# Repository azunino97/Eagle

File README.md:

# Eagle
Public repo for displaying my personal embedded design projects using Eagle, a PCB CAD software!

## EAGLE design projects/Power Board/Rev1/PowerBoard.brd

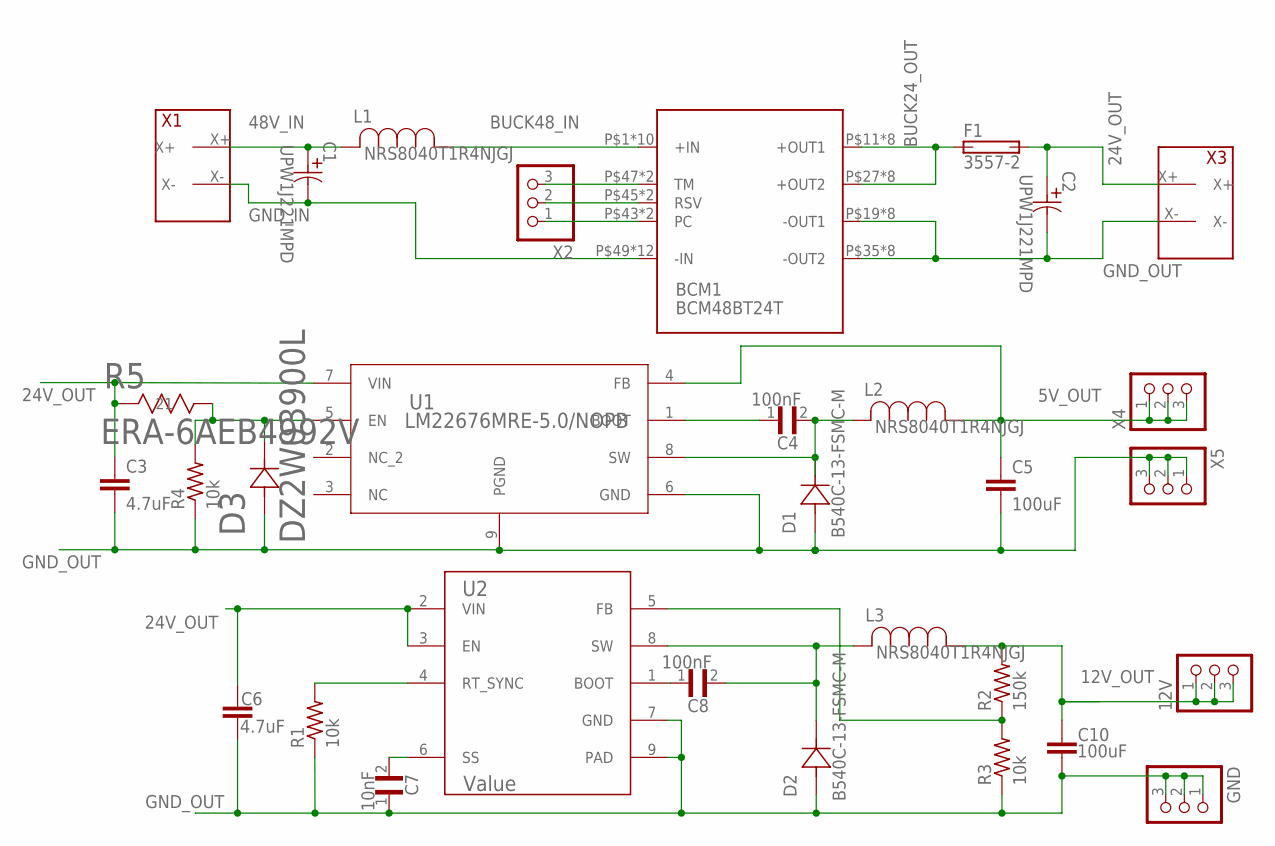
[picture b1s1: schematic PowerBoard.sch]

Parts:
12V: 9-146281-0; TE_9-146281-0
BCM1: BCM48BT24T
C1, C2: UPW1J221MPD; PCAP_10X20-THRU-ELECT
C3, C6: 4.7uF; 0603
C4, C8: 100nF; CAPC2012X135N
C5, C10: 100uF; 1210
C7: 10nF; CAPC2012X135N
D1, D2: B540C-13-FSMC-M; SMC-M
D3: DZ2W03900L; MINI2-F3-B
F1: 3557-2; FUSE_3557-2
GND: 9-146281-0; TE_9-146281-0
L1, L2, L3: NRS8040T1R4NJGJ; IND_TAIYO_NRS8040
R1, R3, R4: 10k; R0603
R2: 150k; R0603
R5: ERA-6AEB4992V; RES_ERA6A_0805
U1: LM22676MRE-5.0/NOPB; MRA08B
U2: Value; DDA0008E_N
X1, X3: XT60
X2, X4, X5: 9-146281-0; TE_9-146281-0

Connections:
5V_OUT: C5.1, L2.1, U1.4 (FB), X4.1, X4.2, X4.3
12V_OUT: 12V.1, 12V.2, 12V.3, C10.1, L3.1, R2.2
24V_OUT: C2.1 (11), C3.1, C6.1, F1.3 (2A), F1.4 (2A), R5.2 (21), U1.7 (VIN), U2.2 (VIN), U2.3 (EN), X3.X+
48V_IN: C1.1 (11), L1.2, X1.X+
BUCK24_OUT: BCM1.P$11 (+OUT1), BCM1.P$12 (+OUT1), BCM1.P$13 (+OUT1), BCM1.P$14 (+OUT1), BCM1.P$15 (+OUT1), BCM1.P$16 (+OUT1), BCM1.P$17 (+OUT1), BCM1.P$18 (+OUT1), BCM1.P$27 (+OUT2), BCM1.P$28 (+OUT2), BCM1.P$29 (+OUT2), BCM1.P$30 (+OUT2), BCM1.P$31 (+OUT2), BCM1.P$32 (+OUT2), BCM1.P$33 (+OUT2), BCM1.P$34 (+OUT2), F1.1 (1A), F1.2 (1A)
BUCK48_IN: BCM1.P$1 (+IN), BCM1.P$2 (+IN), BCM1.P$3 (+IN), BCM1.P$4 (+IN), BCM1.P$5 (+IN), BCM1.P$6 (+IN), BCM1.P$7 (+IN), BCM1.P$8 (+IN), BCM1.P$9 (+IN), BCM1.P$10 (+IN), L1.1
GND_IN: BCM1.P$49 (-IN), BCM1.P$50 (-IN), BCM1.P$51 (-IN), BCM1.P$52 (-IN), BCM1.P$53 (-IN), BCM1.P$54 (-IN), BCM1.P$55 (-IN), BCM1.P$56 (-IN), BCM1.P$57 (-IN), BCM1.P$58 (-IN), BCM1.P$59 (-IN), BCM1.P$60 (-IN), C1.2 (22), X1.X-
GND_OUT: BCM1.P$19 (-OUT1), BCM1.P$20 (-OUT1), BCM1.P$21 (-OUT1), BCM1.P$22 (-OUT1), BCM1.P$23 (-OUT1), BCM1.P$24 (-OUT1), BCM1.P$25 (-OUT1), BCM1.P$26 (-OUT1), BCM1.P$35 (-OUT2), BCM1.P$36 (-OUT2), BCM1.P$37 (-OUT2), BCM1.P$38 (-OUT2), BCM1.P$39 (-OUT2), BCM1.P$40 (-OUT2), BCM1.P$41 (-OUT2), BCM1.P$42 (-OUT2), C2.2 (22), C3.2, C5.2, C6.2, C7.1, C10.2, D1.2 (21), D2.2 (21), D3.2 (22), GND.1, GND.2, GND.3, R1.1, R3.1, R4.1, U1.6 (GND), U1.9 (PGND), U2.7 (GND), U2.9 (PAD), X3.X-, X5.1, X5.2, X5.3
unnamed: C4.1, U1.1 (BOOT)
unnamed: D3.1 (11), R4.2, R5.1 (12), U1.5 (EN)
unnamed: BCM1.P$43 (PC), BCM1.P$44 (PC), X2.1
unnamed: C4.2, D1.1 (12), L2.2, U1.8 (SW)
unnamed: BCM1.P$45 (RSV), BCM1.P$46 (RSV), X2.2
unnamed: BCM1.P$47 (TM), BCM1.P$48 (TM), X2.3
unnamed: C7.2, U2.6 (SS)
unnamed: R1.2, U2.4 (RT_SYNC)
unnamed: C8.1, U2.1 (BOOT)
unnamed: C8.2, D2.1 (12), L3.2, U2.8 (SW)
unnamed: R2.1, R3.2, U2.5 (FB)

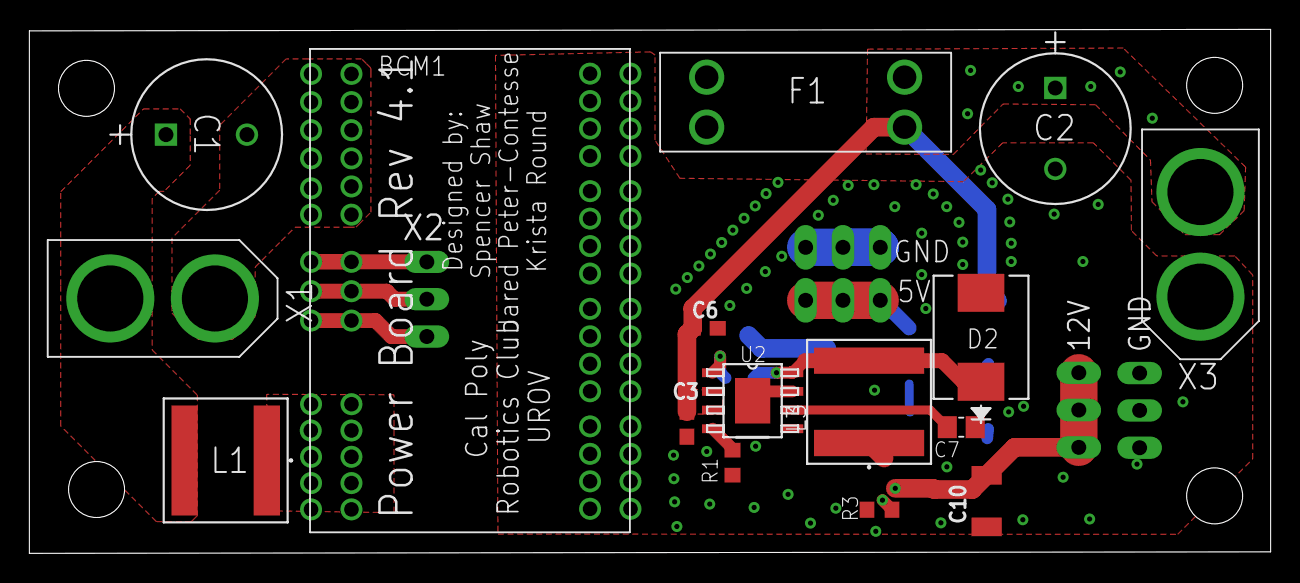
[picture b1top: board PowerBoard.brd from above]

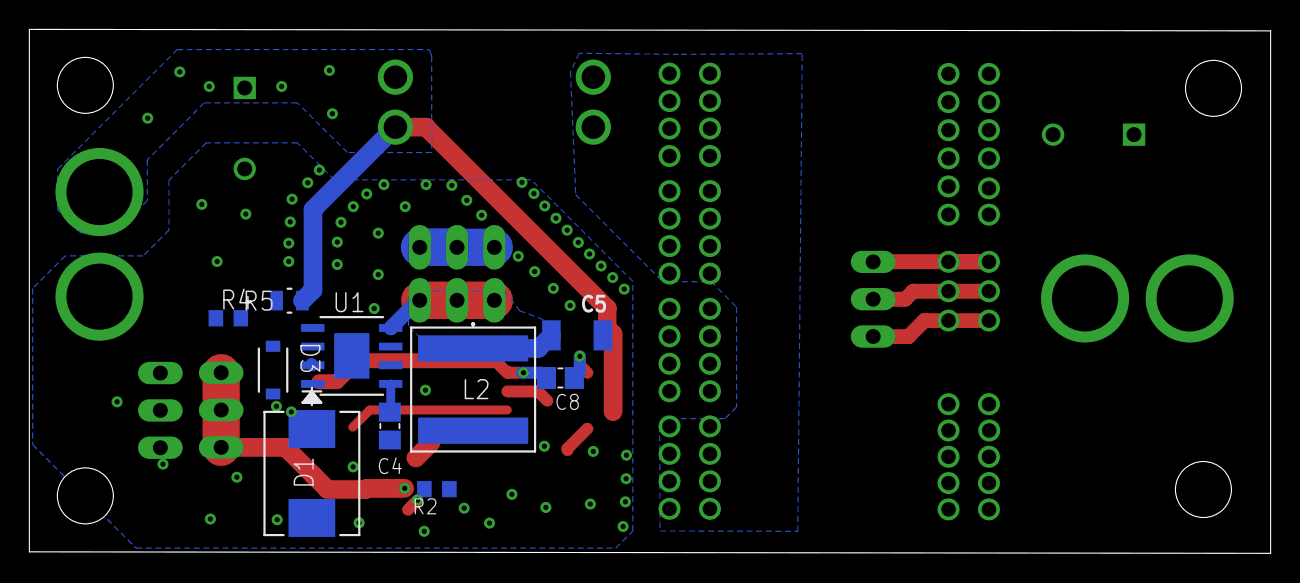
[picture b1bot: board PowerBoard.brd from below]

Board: 2 copper layers, 84.5 x 35.7 mm, 31 parts (12 on the bottom side), 19 nets.

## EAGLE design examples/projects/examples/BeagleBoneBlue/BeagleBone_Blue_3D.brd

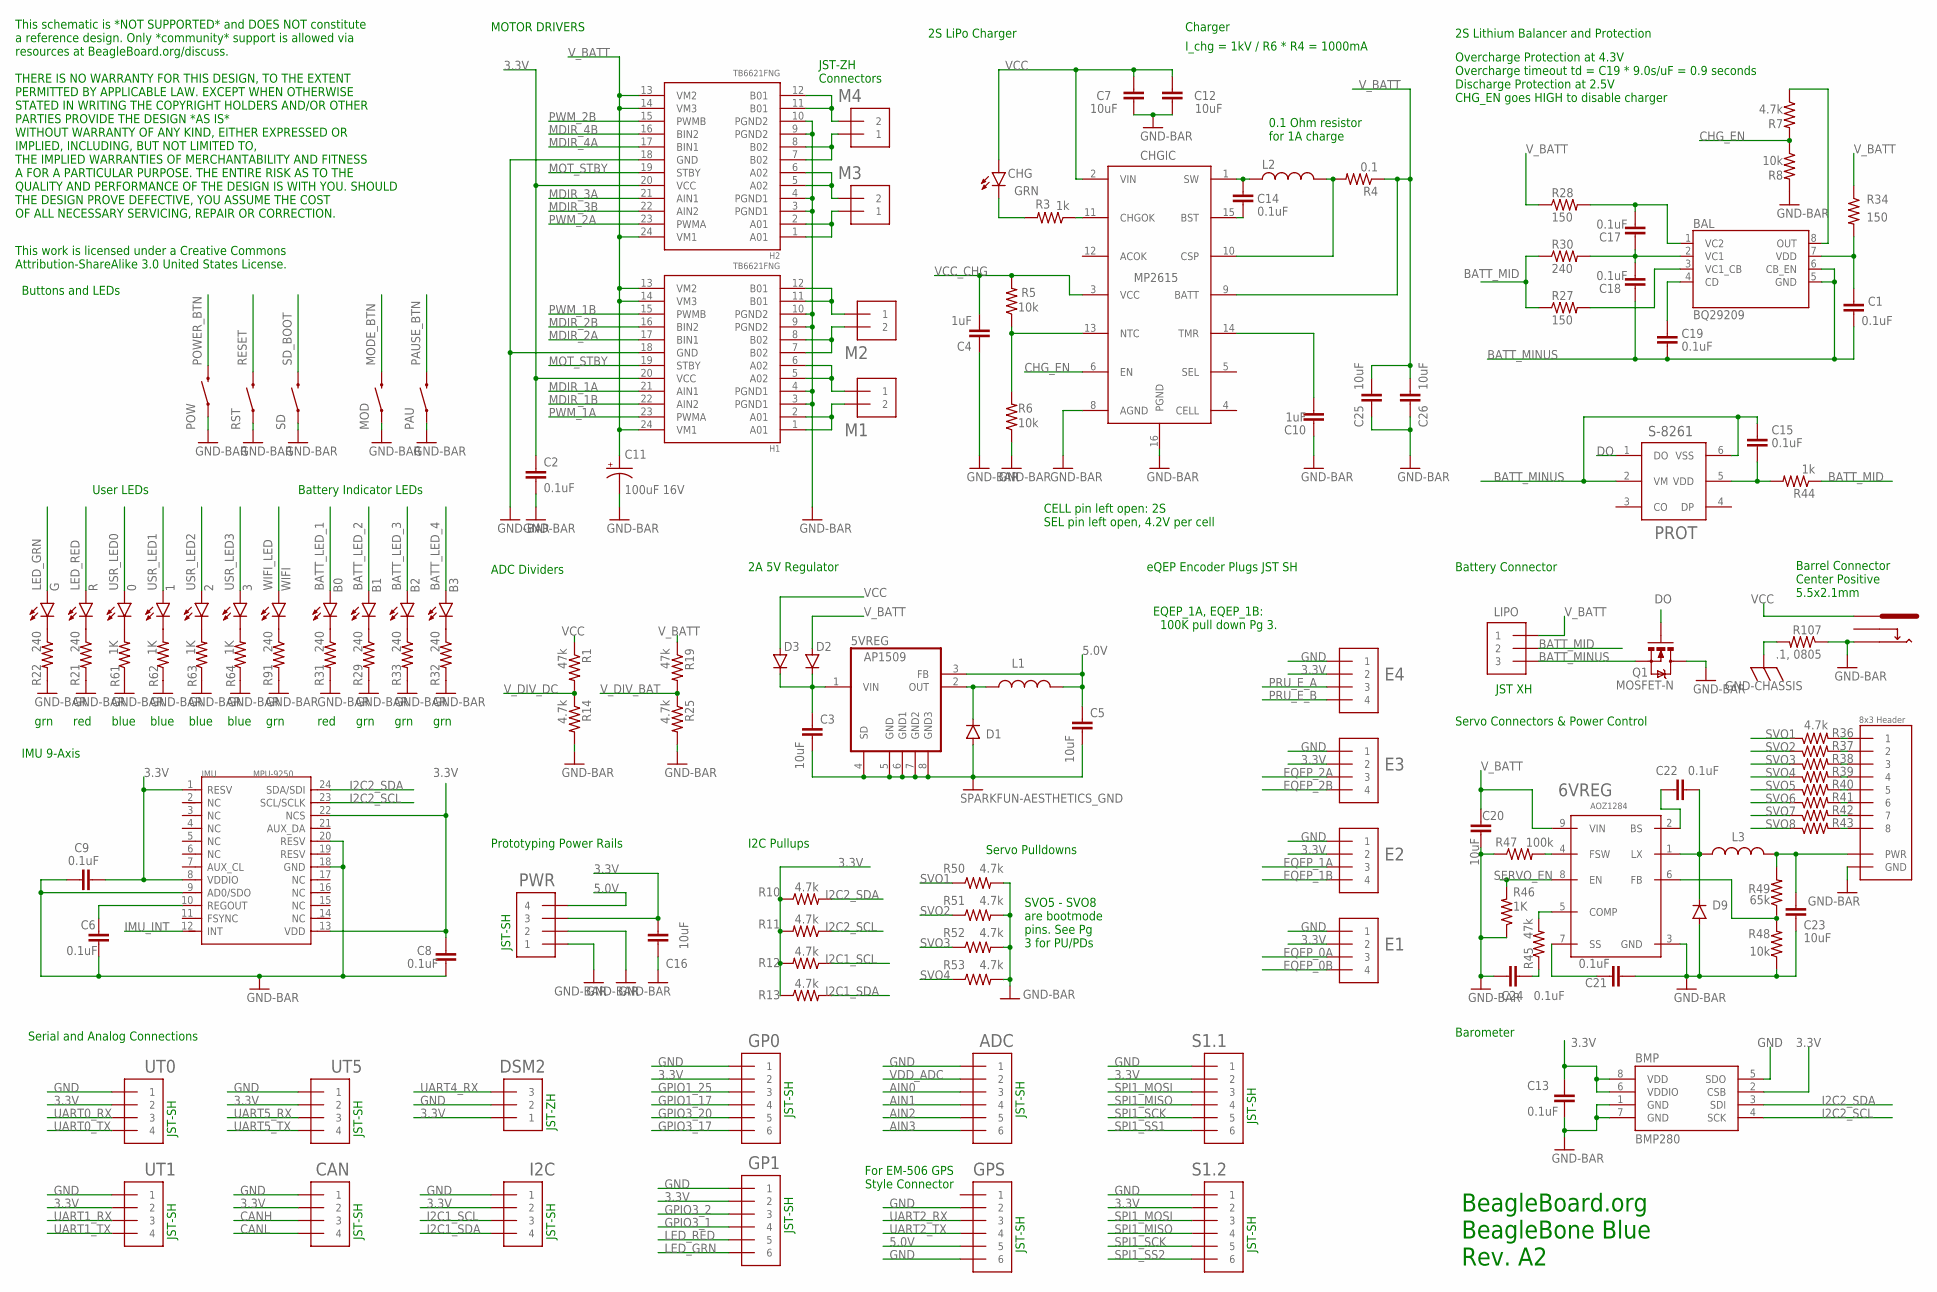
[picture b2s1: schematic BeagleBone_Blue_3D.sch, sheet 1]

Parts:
0, 1, 2, 3: BLUE; 0603-BLUE
5VREG: AP1509SOIC-8-TIGHT; SO08-H
6VREG: AOZ1284; SO08-EXPOSED
12V: PJ-102B_POWER_CON; GHI_PJ-102B_POWER_CON
ADC: JST_SH_6
B0: RED; LED-0603
B1, B2, B3: GREEN; LED-0603
BAL: BQ29209; 8-SON_3X3MM
BMP: BMP280
C1, C2, C6, C8, C9, C13, C14, C15, C17, C18, C19, C21, C22, C24: 0.1uF; 0402-CAP
C3, C5, C7, C12, C16, C20, C23, C25, C26: 10uF; 0805
C4, C10: 1uF; 0402-CAP
C11: 100uF 16V; PANASONIC_D
CAN: JST_SH_4; JST_SH_4_SMD
CHG: GRN; LED-0603
CHGIC: MP2615; QFN50P300X300X100-16
D1, D2, D3: DIODEDIODE-123FL; DIODE_SOD-123FL
D9: DIODEDO214AA; DO-214AA
DSM2: JST_ZH_3
E1, E2, E3, E4: JST_SH_4; JST_SH_4_SMD
G: GREEN; 0603-GREEN
GP0, GP1: JST_SH_6
GPS: JST_SH_6
H1, H2: TB6621FNG; SOP65P760X140-24
I2C: JST_SH_4; JST_SH_4_SMD
IMU: MPU-9250; QFN24G-0.4-3X3MM
J2: SERVO_HEADERS_8X; DIODE_3X8_0.1"_HEADER
L1, L2: 6.8uH; SRN6045
L3: 3.6 uH; INDUCTOR-8X8MM
LIPO: BATTERY; JST_XH_3-PIN
M1, M2, M3, M4: JST_ZH_2
MOD: RS032G05A3SM-SPST-MOMENTARY-SWSMD-1101NE; TACTILE-SWITCH-1101NE
PAU: RS032G05A3SM-SPST-MOMENTARY-SWSMD-1101NE; TACTILE-SWITCH-1101NE
POW: RS032G05A3SM-SPST-MOMENTARY-SWSMD-1101NE; TACTILE-SWITCH-1101NE
PROT: S-8261; SOT-236
PWR: JST_SH_4; JST_SH_4_SMD
Q1: MOSFET-N; SO08-TIGHT
R: RED; 0603-RED
R1, R19, R45: 47k; 0402-RES
R3, R44: 1k; 0402-RES
R4: 0.1; 0402-RES
R5, R6, R8, R48: 10k; 0402-RES
R7, R10, R11, R12, R13, R14, R25, R36, R37, R38, R39, R40, R41, R42, R43, R50, R51, R52, R53: 4.7k; 0402-RES
R21, R22, R29, R30, R31, R32, R33, R91: 240; 0402-RES
R27, R28, R34: 150; 0402-RES
R46, R61, R62, R63, R64: 1K; 0402-RES
R47: 100k; 0402-RES
R49: 65k; 0402-RES
R107: .1, 0805; R0805
RST: RS032G05A3SM-SPST-MOMENTARY-SWSMD-1101NE; TACTILE-SWITCH-1101NE
S1.1, S1.2: JST_SH_6
SD: RS032G05A3SM-SPST-MOMENTARY-SWSMD-1101NE; TACTILE-SWITCH-1101NE
UT0, UT1, UT5: JST_SH_4; JST_SH_4_SMD
WIFI: GREEN; 0603-GREEN

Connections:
3.3V: BMP.2 (CSB), BMP.6 (VDDIO), BMP.8 (VDD), C2.2, C8.1, C9.2, C13.1, C16.1, CAN.2, DSM2.P$1 (1), E1.2, E2.2, E3.2, E4.2, GP0.2, GP1.2, H1.20 (VCC), H2.20 (VCC), I2C.2, IMU.1 (RESV), IMU.8 (VDDIO), IMU.13 (VDD), IMU.22 (NCS), PWR.3, R10.1, R11.2, R12.2, R13.1, S1.1.2, S1.2.2, UT0.2, UT1.2, UT5.2; also elsewhere on the board
5.0V: 5VREG.3 (FB), C5.1, GPS.5, L1.2, PWR.4; also elsewhere on the board
AIN0: ADC.3; also elsewhere on the board
AIN1: ADC.4; also elsewhere on the board
AIN2: ADC.5; also elsewhere on the board
AIN3: ADC.6; also elsewhere on the board
BATT_LED_1: B0.A; also elsewhere on the board
BATT_LED_2: B1.A; also elsewhere on the board
BATT_LED_3: B2.A; also elsewhere on the board
BATT_LED_4: B3.A; also elsewhere on the board
BATT_MID: LIPO.P$2 (2), R27.1, R30.1, R44.1
BATT_MINUS: BAL.5 (GND), BAL.6 (CB_EN), C1.2, C15.1, C18.1, C19.2, LIPO.P$3 (3), PROT.2 (VM), PROT.6 (VSS), Q1.1 (S), Q1.2 (S), Q1.3 (S)
CANH: CAN.3; also elsewhere on the board
CANL: CAN.4; also elsewhere on the board
CGND: R107.2; also elsewhere on the board
CHG_EN: CHGIC.6 (EN), R7.2, R8.1
CO: BAL.8 (OUT), R7.1
DO: PROT.1 (DO), Q1.4 (G)
EQEP_0A: E1.3; also elsewhere on the board
EQEP_0B: E1.4; also elsewhere on the board
EQEP_1A: E2.3; also elsewhere on the board
EQEP_1B: E2.4; also elsewhere on the board
EQEP_2A: E3.3; also elsewhere on the board
EQEP_2B: E3.4; also elsewhere on the board
GND: 5VREG.4 (SD), 5VREG.5 (GND), 5VREG.6 (GND1), 5VREG.7 (GND2), 5VREG.8 (GND3), 6VREG.3 (GND), 12V.OUT, ADC.1, BMP.1 (GND), BMP.5 (SDO), BMP.7 (GND), C2.1, C3.2, C4.1, C5.2, C6.2, C7.2, C8.2, C9.1, C10.1, C11.-, C12.2, C13.2, C16.2, C20.1, C21.1, C23.1, C24.1, C25.2, C26.2, CAN.1, CHGIC.8 (AGND), CHGIC.16 (PGND), D1.A, D9.A, DSM2.P$2 (2), E1.1, E2.1, E3.1, E4.1, GP0.1, GP1.1, GPS.2, GPS.6, H1.3 (PGND1), H1.4 (PGND1), H1.9 (PGND2), H1.10 (PGND2), H1.18 (GND), H2.3 (PGND1), H2.4 (PGND1), H2.9 (PGND2), H2.10 (PGND2), H2.18 (GND), I2C.1, IMU.9 (AD0/SDO), IMU.18 (GND), IMU.20 (RESV), J2.P$13 (GND), J2.P$14 (GND), J2.P$15 (GND), J2.P$16 (GND), J2.P$17 (GND), J2.P$18 (GND), J2.P$23 (GND), J2.P$24 (GND), MOD.1, PAU.1, POW.1, PWR.1, PWR.2, Q1.5 (D), Q1.6 (D), Q1.7 (D), Q1.8 (D), R6.1, R8.2, R14.2, R21.2, R22.2, R25.2, R29.2, R31.2, R32.2, R33.2, R46.1, R47.1, R48.1, R50.2, R51.2, R52.2, R53.2, R61.1, R62.1, R63.1, R64.1, R91.2, R107.1, RST.1, S1.1.1, S1.2.1, SD.1, UT0.1, UT1.1, UT5.1; also elsewhere on the board
GPIO1_17: GP0.4; also elsewhere on the board
GPIO1_25: GP0.3; also elsewhere on the board
GPIO3_1: GP1.4; also elsewhere on the board
GPIO3_2: GP1.3; also elsewhere on the board
GPIO3_17: GP0.6; also elsewhere on the board
GPIO3_20: GP0.5; also elsewhere on the board
I2C1_SCL: I2C.3, R12.1; also elsewhere on the board
I2C1_SDA: I2C.4, R13.2; also elsewhere on the board
I2C2_SCL: BMP.4 (SCK), IMU.23 (SCL/SCLK), R11.1; also elsewhere on the board
I2C2_SDA: BMP.3 (SDI), IMU.24 (SDA/SDI), R10.2; also elsewhere on the board
IMU_INT: IMU.12 (INT); also elsewhere on the board
L3: B2.C, R33.1
L4: B3.C, R32.1
LED_GRN: G.A, GP1.6; also elsewhere on the board
LED_RED: GP1.5, R.A; also elsewhere on the board
MDIR_1A: H1.21 (AIN1); also elsewhere on the board
MDIR_1B: H1.22 (AIN2); also elsewhere on the board
MDIR_2A: H1.17 (BIN1); also elsewhere on the board
MDIR_2B: H1.16 (BIN2); also elsewhere on the board
MDIR_3A: H2.21 (AIN1); also elsewhere on the board
MDIR_3B: H2.22 (AIN2); also elsewhere on the board
MDIR_4A: H2.17 (BIN1); also elsewhere on the board
MDIR_4B: H2.16 (BIN2); also elsewhere on the board
MODE_BTN: MOD.2; also elsewhere on the board
MOT1A: H1.1 (A01), H1.2 (A01), M1.P$2 (2)
MOT1B: H1.5 (A02), H1.6 (A02), M1.P$1 (1)
MOT2A: H1.11 (B01), H1.12 (B01), M2.P$1 (1)
MOT2B: H1.7 (B02), H1.8 (B02), M2.P$2 (2)
MOT3A: H2.1 (A01), H2.2 (A01), M3.P$1 (1)
MOT3B: H2.5 (A02), H2.6 (A02), M3.P$2 (2)
MOT4A: H2.11 (B01), H2.12 (B01), M4.P$2 (2)
MOT4B: H2.7 (B02), H2.8 (B02), M4.P$1 (1)
MOT_STBY: H1.19 (STBY), H2.19 (STBY); also elsewhere on the board
unnamed: J2.P$1 (1), R36.2
unnamed: G.C, R22.1
unnamed: BAL.2 (VC1), C17.1, C18.2, R30.2
unnamed: R.C, R21.1
unnamed: BAL.1 (VC2), C17.2, R28.2
unnamed: 6VREG.7 (SS), C21.2
unnamed: C15.2, PROT.5 (VDD), R44.2
unnamed: C6.1, IMU.10 (REGOUT)
unnamed: C14.1, CHGIC.15 (BST)
unnamed: 5VREG.2 (OUT), D1.C, L1.1
unnamed: CHG.C, R3.2
unnamed: CHGIC.11 (CHGOK), R3.1
unnamed: R91.1, WIFI.C
unnamed: BAL.4 (CD), C19.1
unnamed: J2.P$2 (2), R37.2
unnamed: BAL.7 (VDD), C1.1, R34.2
unnamed: J2.P$3 (3), R38.2
unnamed: J2.P$4 (4), R39.2
unnamed: 0.C, R61.2
unnamed: B1.C, R29.1
unnamed: B0.C, R31.1
unnamed: BAL.3 (VC1_CB), R27.2
unnamed: J2.P$5 (5), R40.2
unnamed: J2.P$6 (6), R41.2
unnamed: 6VREG.2 (BS), C22.1
unnamed: J2.P$19 (7), R42.2
unnamed: C14.2, CHGIC.1 (SW), L2.1
unnamed: J2.P$20 (8), R43.2
unnamed: 1.C, R62.2
unnamed: 2.C, R63.2
unnamed: 3.C, R64.2
unnamed: 6VREG.1 (LX), C22.2, D9.C, L3.1
unnamed: 6VREG.4 (FSW), R47.2
unnamed: C23.2, J2.P$7 (PWR), J2.P$8 (PWR), J2.P$9 (PWR), J2.P$10 (PWR), J2.P$11 (PWR), J2.P$12 (PWR), J2.P$21 (PWR), J2.P$22 (PWR), L3.2, R49.2
unnamed: 6VREG.5 (COMP), R45.2
unnamed: 6VREG.6 (FB), R48.2, R49.1
unnamed: C24.2, R45.1
unnamed: CHGIC.10 (CSP), L2.2, R4.2
unnamed: C10.2, CHGIC.14 (TMR)
unnamed: CHGIC.13 (NTC), R5.1, R6.2
unnamed: 5VREG.1 (VIN), C3.1, D2.C, D3.C
PAUSE_BTN: PAU.2; also elsewhere on the board
POWER_BTN: POW.2; also elsewhere on the board
PRU_E_A: E4.3; also elsewhere on the board
PRU_E_B: E4.4; also elsewhere on the board
PWM_1A: H1.23 (PWMA); also elsewhere on the board
PWM_1B: H1.15 (PWMB); also elsewhere on the board
PWM_2A: H2.23 (PWMA); also elsewhere on the board
PWM_2B: H2.15 (PWMB); also elsewhere on the board
RESET: RST.2; also elsewhere on the board
SD_BOOT: SD.2; also elsewhere on the board
SERVO_EN: 6VREG.8 (EN), R46.2; also elsewhere on the board
SPI1_MISO: S1.1.4, S1.2.4; also elsewhere on the board
SPI1_MOSI: S1.1.3, S1.2.3; also elsewhere on the board
SPI1_SCK: S1.1.5, S1.2.5; also elsewhere on the board
SPI1_SS1: S1.1.6; also elsewhere on the board
SPI1_SS2: S1.2.6; also elsewhere on the board
SVO1: R36.1, R50.1; also elsewhere on the board
SVO2: R37.1, R51.1; also elsewhere on the board
SVO3: R38.1, R52.1; also elsewhere on the board
SVO4: R39.1, R53.1; also elsewhere on the board
SVO5: R40.1; also elsewhere on the board
SVO6: R41.1; also elsewhere on the board
SVO7: R42.1; also elsewhere on the board
SVO8: R43.1; also elsewhere on the board
UART0_RX: UT0.3; also elsewhere on the board
UART0_TX: UT0.4; also elsewhere on the board
UART1_RX: UT1.3; also elsewhere on the board
UART1_TX: UT1.4; also elsewhere on the board
UART2_RX: GPS.3; also elsewhere on the board
UART2_TX: GPS.4; also elsewhere on the board
UART4_RX: DSM2.P$3 (3); also elsewhere on the board
UART5_RX: UT5.3; also elsewhere on the board
UART5_TX: UT5.4; also elsewhere on the board
USR_LED0: 0.A; also elsewhere on the board
USR_LED1: 1.A; also elsewhere on the board
USR_LED2: 2.A; also elsewhere on the board
USR_LED3: 3.A; also elsewhere on the board
VCC: 12V.IN, C7.1, C12.1, CHG.A, CHGIC.2 (VIN), D3.A, R1.1
VCC_CHG: C4.2, CHGIC.3 (VCC), R5.2
VDD_ADC: ADC.2; also elsewhere on the board
V_BATT: 6VREG.9 (VIN), C11.+, C20.2, C25.1, C26.1, CHGIC.9 (BATT), D2.A, H1.13 (VM2), H1.14 (VM3), H1.24 (VM1), H2.13 (VM2), H2.14 (VM3), H2.24 (VM1), LIPO.P$1 (1), R4.1, R19.1, R28.1, R34.1
V_DIV_BAT: R19.2, R25.1; also elsewhere on the board
V_DIV_DC: R1.2, R14.1; also elsewhere on the board
WIFI_LED: WIFI.A; also elsewhere on the board

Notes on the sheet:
BeagleBoard.org BeagleBone Blue Rev. A2
Barrel Connector Center Positive 5.5x2.1mm
ADC Dividers
Prototyping Power Rails
Buttons and LEDs
eQEP Encoder Plugs JST SH
I2C Pullups
2A 5V Regulator
Overcharge Protection at 4.3V Overcharge timeout td = C19 * 9.0s/uF = 0.9 seconds Discharge Protection at 2.5V CHG_EN goes HIGH to disable charger
I_chg = 1kV / R6 * R4 = 1000mA
Battery Indicator LEDs
MOTOR DRIVERS
Servo Connectors & Power Control
JST-ZH
Barometer
Charger
JST-ZH Connectors
IMU 9-Axis
For EM-506 GPS Style Connector
2S Lithium Balancer and Protection
red
grn
JST XH
Battery Connector
JST-SH
Serial and Analog Connections
Servo Pulldowns
2S LiPo Charger
0.1 Ohm resistor for 1A charge
CELL pin left open: 2S SEL pin left open, 4.2V per cell
This schematic is *NOT SUPPORTED* and DOES NOT constitute a reference design. Only *community* support is allowed via resources at BeagleBoard.org/discuss. THERE IS NO WARRANTY FOR THIS DESIGN, TO THE EXTENT PERMITTED BY APPLICABLE LAW. EXCEPT WHEN OTHERWISE STATED IN WRITING THE COPYRIGHT HOLDERS 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
This work is licensed under a Creative Commons Attribution-ShareAlike 3.0 United States License.
User LEDs
blue
EQEP_1A, EQEP_1B: 100K pull down Pg 3.
SVO5 - SVO8 are bootmode pins. See Pg 3 for PU/PDs

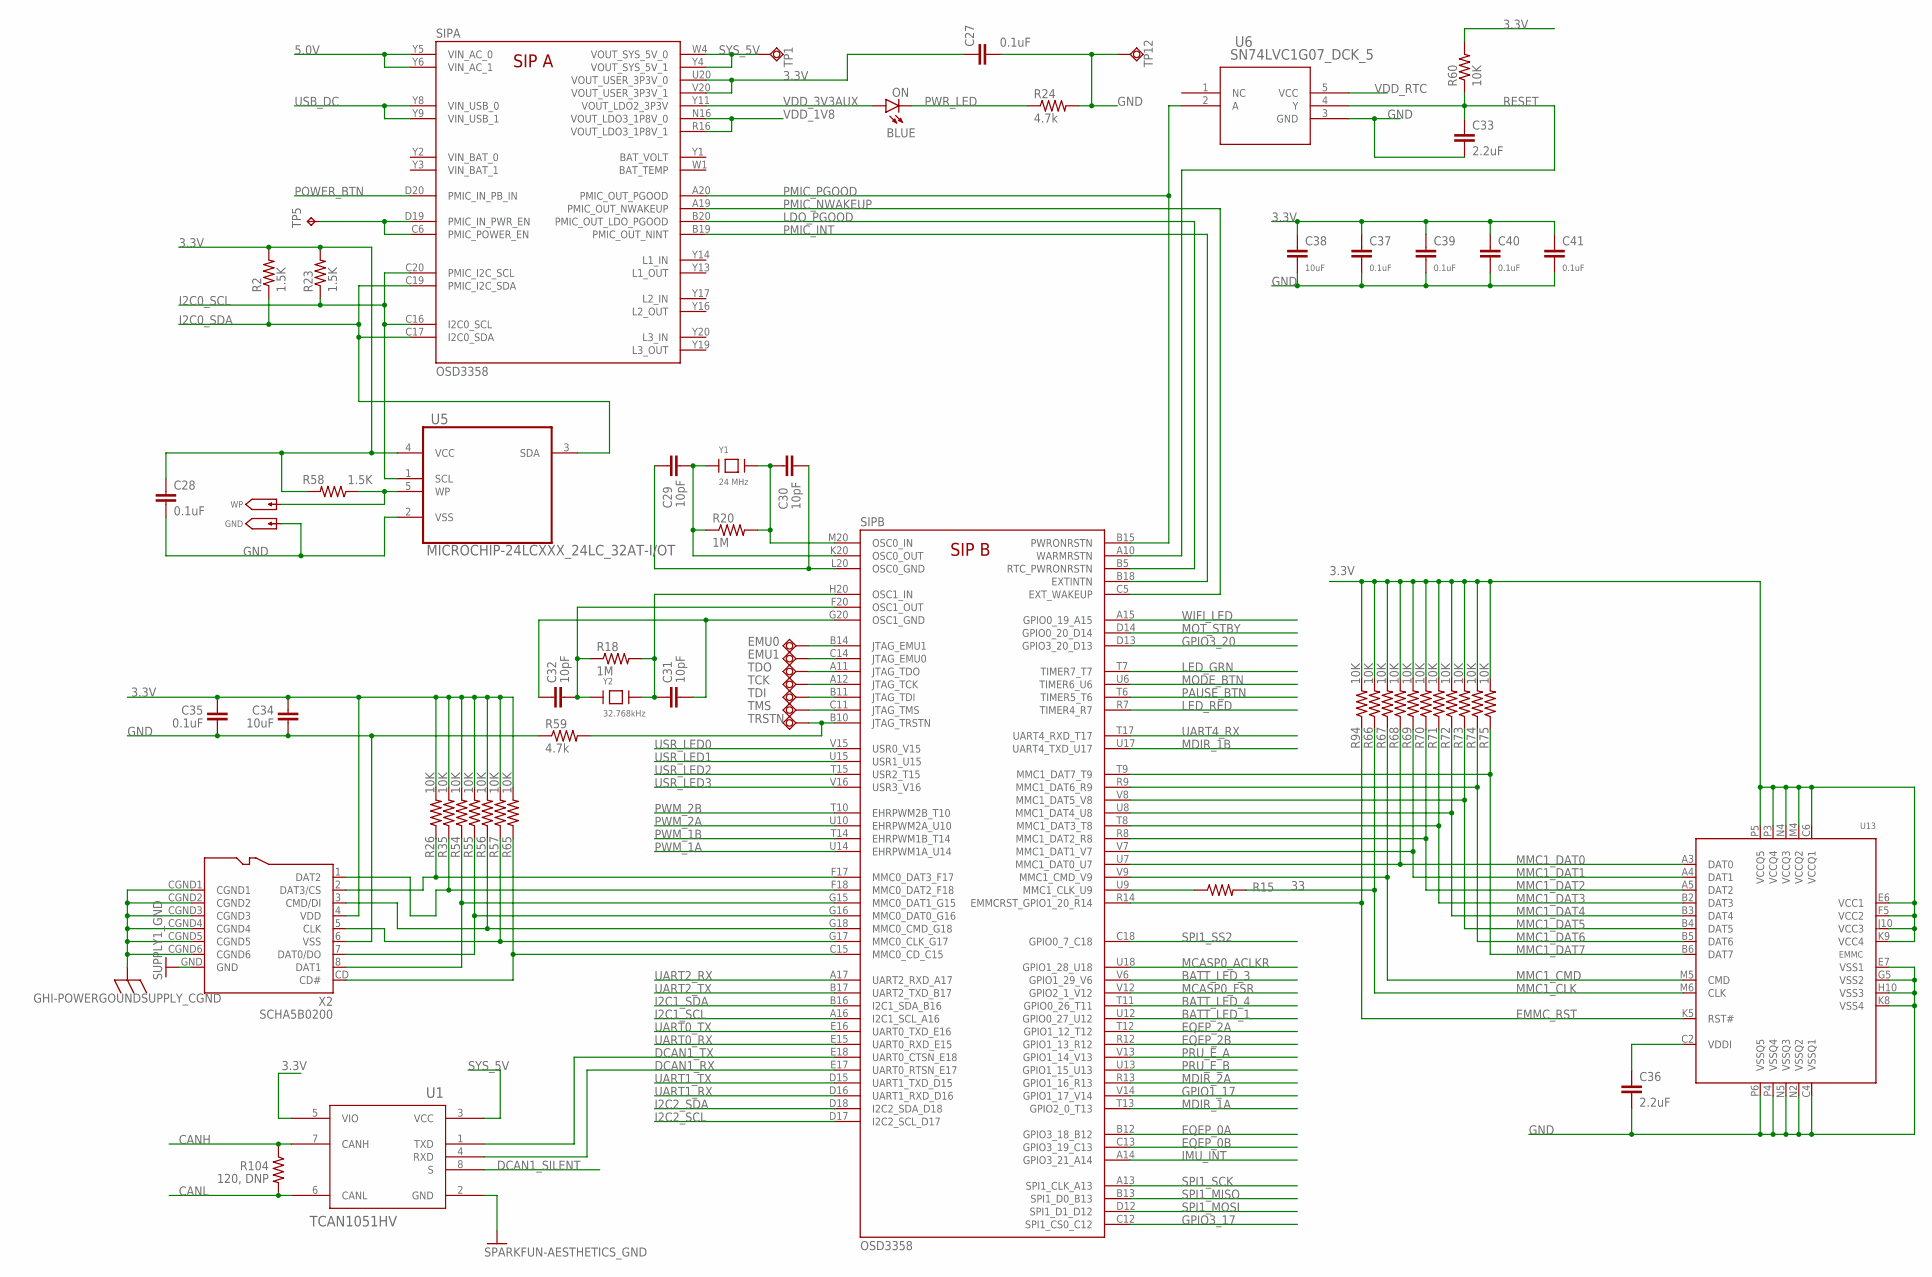
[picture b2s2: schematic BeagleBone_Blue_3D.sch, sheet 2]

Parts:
C27, C28, C35, C37, C39, C40, C41: 0.1uF; 0402-CAP
C29, C30, C31, C32: 10pF; 0402-CAP
C33, C36: 2.2uF; 0402-CAP
C34, C38: 10uF; 0805
EMU0, EMU1: TESTPAD_TPSQB1,27; TESTPAD_B1,27
GND: TESTPAD/W_HOLE_1X1; DIODE_GHI2_TESTPAD/W_HOLE_1X1
ON: BLUE; BEAGLEBONE_BLUE_BEAGLEBONE_BLUE_LED-0603
R2, R23, R58: 1.5K; 0402-RES
R15: 33; 0402-RES
R18, R20: 1M; 0402-RES
R24, R59: 4.7k; 0402-RES
R26, R35, R54, R55, R56, R57, R60, R65, R66, R67, R68, R69, R70, R71, R72, R73, R74, R75, R94: 10K; 0402-RES
R104: 120, DNP; R0603
SIP: OSD3358
TCK: TESTPAD_TPSQB1,27; TESTPAD_B1,27
TDI: TESTPAD_TPSQB1,27; TESTPAD_B1,27
TDO: TESTPAD_TPSQB1,27; TESTPAD_B1,27
TMS: TESTPAD_TPSQB1,27; TESTPAD_B1,27
TP1, TP12: TESTPAD_TPSQB1,27; TESTPAD_B1,27
TP5: TPB0,65; B0,65
TRSTN: TESTPAD_TPSQB1,27; TESTPAD_B1,27
U1: TCAN1051HV; D8
U5: MICROCHIP-24LCXXX_24LC_32AT-I/OT; MICROCHIP-24LCXXX_SOT95P290X145-5N
U6: SN74LVC1G07_DCK_5; DCK5
U13: EMMC; MICRON_EMMC_153
WP: TESTPAD/W_HOLE_1X1; DIODE_GHI2_TESTPAD/W_HOLE_1X1
X2: SCHA5B0200; GHI-CONNECTORS_SCHA5B0200
Y1: 24 MHz; GHI2_CRYSTAL_5X3.2MM
Y2: 32.768kHz; GHI2_CRYSTAL_3.2X1.5

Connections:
3.3V: C27.1, C28.1, C34.2, C35.2, C37.1, C38.1, C39.1, C40.1, C41.1, R2.2, R23.2, R26.2, R35.2, R54.2, R55.2, R56.2, R57.2, R58.2, R60.2, R65.2, R66.2, R67.2, R68.2, R69.2, R70.2, R71.2, R72.2, R73.2, R74.2, R75.2, R94.2, SIP.U20 (VOUT_USER_3P3V_0), SIP.V20 (VOUT_USER_3P3V_1), U1.5 (VIO), U5.4 (VCC), U13.C6 (VCCQ1), U13.E6 (VCC1), U13.F5 (VCC2), U13.J10 (VCC3), U13.K9 (VCC4), U13.M4 (VCCQ2), U13.N4 (VCCQ3), U13.P3 (VCCQ4), U13.P5 (VCCQ5), X2.4 (VDD); also elsewhere on the board
5.0V: SIP.Y5 (VIN_AC_0), SIP.Y6 (VIN_AC_1); also elsewhere on the board
BATT_LED_1: SIP.U12 (GPIO0_27_U12); also elsewhere on the board
BATT_LED_3: SIP.V6 (GPIO1_29_V6); also elsewhere on the board
BATT_LED_4: SIP.T11 (GPIO0_26_T11); also elsewhere on the board
CANH: R104.1, U1.7 (CANH); also elsewhere on the board
CANL: R104.2, U1.6 (CANL); also elsewhere on the board
CGND: X2.CGND1, X2.CGND2, X2.CGND3, X2.CGND4, X2.CGND5, X2.CGND6; also elsewhere on the board
DCAN1_RX: SIP.E17 (UART0_RTSN_E17), U1.4 (RXD)
DCAN1_SILENT: U1.8 (S); also elsewhere on the board
DCAN1_TX: SIP.E18 (UART0_CTSN_E18), U1.1 (TXD)
EMMC_RST: R94.1, SIP.R14 (EMMCRST_GPIO1_20_R14), U13.K5 (RST#)
EQEP_0A: SIP.B12 (GPIO3_18_B12); also elsewhere on the board
EQEP_0B: SIP.C13 (GPIO3_19_C13); also elsewhere on the board
EQEP_2A: SIP.T12 (GPIO1_12_T12); also elsewhere on the board
EQEP_2B: SIP.R12 (GPIO1_13_R12); also elsewhere on the board
GND: C27.2, C28.2, C33.2, C34.1, C35.1, C36.2, C37.2, C38.2, C39.2, C40.2, C41.2, GND.P$1, R24.2, R59.1, TP12.TP, U1.2 (GND), U5.2 (VSS), U6.3 (GND), U13.C4 (VSSQ1), U13.E7 (VSS1), U13.G5 (VSS2), U13.H10 (VSS3), U13.K8 (VSS4), U13.N2 (VSSQ2), U13.N5 (VSSQ3), U13.P4 (VSSQ4), U13.P6 (VSSQ5), X2.6 (VSS), X2.GND; also elsewhere on the board
GPIO1_17: SIP.V14 (GPIO1_17_V14); also elsewhere on the board
GPIO3_17: SIP.C12 (SPI1_CS0_C12); also elsewhere on the board
GPIO3_20: SIP.D13 (GPIO3_20_D13); also elsewhere on the board
I2C0_SCL: R23.1, SIP.C16 (I2C0_SCL), SIP.C20 (PMIC_I2C_SCL), U5.1 (SCL)
I2C0_SDA: R2.1, SIP.C17 (I2C0_SDA), SIP.C19 (PMIC_I2C_SDA), U5.3 (SDA)
I2C1_SCL: SIP.A16 (I2C1_SCL_A16); also elsewhere on the board
I2C1_SDA: SIP.B16 (I2C1_SDA_B16); also elsewhere on the board
I2C2_SCL: SIP.D17 (I2C2_SCL_D17); also elsewhere on the board
I2C2_SDA: SIP.D18 (I2C2_SDA_D18); also elsewhere on the board
IMU_INT: SIP.A14 (GPIO3_21_A14); also elsewhere on the board
LDO_PGOOD: SIP.B5 (RTC_PWRONRSTN), SIP.B20 (PMIC_OUT_LDO_PGOOD)
LED_GRN: SIP.T7 (TIMER7_T7); also elsewhere on the board
LED_RED: SIP.R7 (TIMER4_R7); also elsewhere on the board
MCASP0_ACLKR: SIP.U18 (GPIO1_28_U18); also elsewhere on the board
MCASP0_FSR: SIP.V12 (GPIO2_1_V12); also elsewhere on the board
MDIR_1A: SIP.T13 (GPIO2_0_T13); also elsewhere on the board
MDIR_1B: SIP.U17 (UART4_TXD_U17); also elsewhere on the board
MDIR_2A: SIP.R13 (GPIO1_16_R13); also elsewhere on the board
MMC1_CLK: R15.2, R66.1, U13.M6 (CLK)
MMC1_CMD: R67.1, SIP.V9 (MMC1_CMD_V9), U13.M5 (CMD)
MMC1_DAT0: R68.1, SIP.U7 (MMC1_DAT0_U7), U13.A3 (DAT0)
MMC1_DAT1: R69.1, SIP.V7 (MMC1_DAT1_V7), U13.A4 (DAT1)
MMC1_DAT2: R70.1, SIP.R8 (MMC1_DAT2_R8), U13.A5 (DAT2)
MMC1_DAT3: R71.1, SIP.T8 (MMC1_DAT3_T8), U13.B2 (DAT3)
MMC1_DAT4: R72.1, SIP.U8 (MMC1_DAT4_U8), U13.B3 (DAT4)
MMC1_DAT5: R73.1, SIP.V8 (MMC1_DAT5_V8), U13.B4 (DAT5)
MMC1_DAT6: R74.1, SIP.R9 (MMC1_DAT6_R9), U13.B5 (DAT6)
MMC1_DAT7: R75.1, SIP.T9 (MMC1_DAT7_T9), U13.B6 (DAT7)
MODE_BTN: SIP.U6 (TIMER6_U6); also elsewhere on the board
MOT_STBY: SIP.D14 (GPIO0_20_D14); also elsewhere on the board
unnamed: R57.1, SIP.G17 (MMC0_CLK_G17), X2.5 (CLK)
unnamed: R26.1, SIP.F17 (MMC0_DAT3_F17), X2.2 (DAT3/CS)
unnamed: SIP.C6 (PMIC_POWER_EN), SIP.D19 (PMIC_IN_PWR_EN), TP5.TP
unnamed: C30.1, R20.2, SIP.M20 (OSC0_IN), Y1.2
unnamed: C29.1, R20.1, SIP.K20 (OSC0_OUT), Y1.1
unnamed: R58.1, U5.5 (WP), WP.P$1
unnamed: C29.2, C30.2, SIP.L20 (OSC0_GND)
unnamed: C31.1, R18.2, SIP.H20 (OSC1_IN), Y2.P$2
unnamed: C32.2, R18.1, SIP.F20 (OSC1_OUT), Y2.P$1
unnamed: C31.2, C32.1, SIP.G20 (OSC1_GND)
unnamed: EMU0.TP, SIP.B14 (JTAG_EMU1)
unnamed: EMU1.TP, SIP.C14 (JTAG_EMU0)
unnamed: SIP.A11 (JTAG_TDO), TDO.TP
unnamed: SIP.A12 (JTAG_TCK), TCK.TP
unnamed: SIP.B11 (JTAG_TDI), TDI.TP
unnamed: SIP.C11 (JTAG_TMS), TMS.TP
unnamed: R59.2, SIP.B10 (JTAG_TRSTN), TRSTN.TP
unnamed: R54.1, SIP.G15 (MMC0_DAT1_G15), X2.8 (DAT1)
unnamed: R56.1, SIP.G18 (MMC0_CMD_G18), X2.3 (CMD/DI)
unnamed: R65.1, SIP.C15 (MMC0_CD_C15), X2.CD (CD#)
unnamed: R55.1, SIP.G16 (MMC0_DAT0_G16), X2.7 (DAT0/DO)
unnamed: C36.1, U13.C2 (VDDI)
unnamed: R15.1, SIP.U9 (MMC1_CLK_U9)
NTE: R35.1, SIP.F18 (MMC0_DAT2_F18), X2.1 (DAT2)
PAUSE_BTN: SIP.T6 (TIMER5_T6); also elsewhere on the board
PMIC_INT: SIP.B18 (EXTINTN), SIP.B19 (PMIC_OUT_NINT)
PMIC_NWAKEUP: SIP.A19 (PMIC_OUT_NWAKEUP), SIP.C5 (EXT_WAKEUP)
PMIC_PGOOD: SIP.A20 (PMIC_OUT_PGOOD), SIP.B15 (PWRONRSTN), U6.2 (A)
POWER_BTN: SIP.D20 (PMIC_IN_PB_IN); also elsewhere on the board
PRU_E_A: SIP.V13 (GPIO1_14_V13); also elsewhere on the board
PRU_E_B: SIP.U13 (GPIO1_15_U13); also elsewhere on the board
PWM_1A: SIP.U14 (EHRPWM1A_U14); also elsewhere on the board
PWM_1B: SIP.T14 (EHRPWM1B_T14); also elsewhere on the board
PWM_2A: SIP.U10 (EHRPWM2A_U10); also elsewhere on the board
PWM_2B: SIP.T10 (EHRPWM2B_T10); also elsewhere on the board
PWR_LED: ON.C, R24.1
RESET: C33.1, R60.1, SIP.A10 (WARMRSTN), U6.4 (Y); also elsewhere on the board
SPI1_MISO: SIP.B13 (SPI1_D0_B13); also elsewhere on the board
SPI1_MOSI: SIP.D12 (SPI1_D1_D12); also elsewhere on the board
SPI1_SCK: SIP.A13 (SPI1_CLK_A13); also elsewhere on the board
SPI1_SS2: SIP.C18 (GPIO0_7_C18); also elsewhere on the board
SYS_5V: SIP.W4 (VOUT_SYS_5V_0), SIP.Y4 (VOUT_SYS_5V_1), TP1.TP, U1.3 (VCC); also elsewhere on the board
UART0_RX: SIP.E15 (UART0_RXD_E15); also elsewhere on the board
UART0_TX: SIP.E16 (UART0_TXD_E16); also elsewhere on the board
UART1_RX: SIP.D16 (UART1_RXD_D16); also elsewhere on the board
UART1_TX: SIP.D15 (UART1_TXD_D15); also elsewhere on the board
UART2_RX: SIP.A17 (UART2_RXD_A17); also elsewhere on the board
UART2_TX: SIP.B17 (UART2_TXD_B17); also elsewhere on the board
UART4_RX: SIP.T17 (UART4_RXD_T17); also elsewhere on the board
USB_DC: SIP.Y8 (VIN_USB_0), SIP.Y9 (VIN_USB_1); also elsewhere on the board
USR_LED0: SIP.V15 (USR0_V15); also elsewhere on the board
USR_LED1: SIP.U15 (USR1_U15); also elsewhere on the board
USR_LED2: SIP.T15 (USR2_T15); also elsewhere on the board
USR_LED3: SIP.V16 (USR3_V16); also elsewhere on the board
VDD_1V8: SIP.N16 (VOUT_LDO3_1P8V_0), SIP.R16 (VOUT_LDO3_1P8V_1); also elsewhere on the board
VDD_3V3AUX: ON.A, SIP.Y11 (VOUT_LDO2_3P3V)
VDD_RTC: U6.5 (VCC); also elsewhere on the board
VIN_BAT_0: SIP.Y2 (VIN_BAT_0)
VIN_BAT_1: SIP.Y3 (VIN_BAT_1)
WIFI_LED: SIP.A15 (GPIO0_19_A15); also elsewhere on the board

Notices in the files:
parts and their libraries:
SparkFun-Capacitors: Licensing: Creative Commons ShareAlike 4.0 International - https://creativecommons.org/licenses/by-sa/4.0
SparkFun-Aesthetics: Released under the Creative Commons Attribution Share-Alike 4.0 License
SparkFun-Aesthetics: https://creativecommons.org/licenses/by-sa/4.0
